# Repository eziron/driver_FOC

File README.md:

# EZFOC V1 - Controlador FOC para Motores Brushless

<p align="center">
  
  <br>
  <em>Vista frontal de la PCB EZFOC V1 completamente ensamblada.</em>
</p>

---

## 📜 Descripción General

**EZFOC V1** es mi proyecto de título con el cual obtuve el grado de Ingeniero de Ejecución en Electrónica. El proyecto se enfoca en el diseño, implementación y validación de un controlador de campo orientado (FOC) para motores brushless (BLDC), desarrollado desde cero abarcando tanto el diseño del **hardware (PCB)** como la programación del **firmware** en un microcontrolador de alto rendimiento **STM32H743VIT6**.

El principal objetivo del proyecto fue ofrecer una solución robusta y de altas prestaciones para aplicaciones exigentes, como la **robótica de competencia (robots de sumo)**, donde el control preciso de torque y velocidad, junto con la capacidad de manejar altas corrientes, es fundamental.

Para una referencia completa y detallada, puedes consultar el **[Esquemático del Hardware](esquematico%20PCB.pdf)** y el **[Manuscrito del Proyecto de Título](manuscrito%20Driver%20FOC%20rev%203%20300325.pdf)**, ambos disponibles en la raíz de este repositorio.

### ✨ Características Principales

*   **Control FOC (Field-Oriented Control):** Permite un control de torque suave y eficiente, desacoplando el flujo magnético del par motor.
*   **Hardware Personalizado:**
    *   PCB de 4 capas diseñada en Autodesk Eagle. Una parte del ensamblaje se realizó mediante el servicio de **PCBA de JLCPCB**, mientras que los componentes restantes fueron soldados manualmente.
    *   Inversor trifásico capaz de manejar altas corrientes (hasta 100A continuos por diseño, con MOSFETs en paralelo).
    *   Medición de corriente de fase **en línea (inline)**, a la salida de cada pierna del inversor, con resistencias shunt y amplificadores INA240.
    *   Soporte para encoder magnético (AS5047P) para una realimentación de posición precisa.
*   **Firmware de Alto Rendimiento:**
    *   Basado en un microcontrolador **STM32H743VIT6** (ARM Cortex-M7 @ 480 MHz).
    *   Lazo de control ejecutado a **48 kHz** en una interrupción de alta prioridad para garantizar el tiempo real.
    *   Uso intensivo de periféricos como Timers, ADC y DMA para minimizar la carga de la CPU.
    *   Comunicación USB (Virtual COM Port) para depuración y visualización de datos en tiempo real.
*   **Diseño Mecánico:** Incluye soportes y acoples para el motor y el encoder diseñados en Autodesk Inventor e impresos en 3D.

---

## 📂 Estructura del Repositorio

El repositorio está organizado en varios directorios clave que separan las diferentes partes del proyecto. Para un acceso rápido, el **esquemático final** (`esquematico PCB.pdf`) y el **manuscrito del proyecto** (`manuscrito Driver FOC...pdf`) se encuentran en la raíz del repositorio.

```
.
├── Firmware_H7/      # Código fuente del firmware para el STM32H7.
├── Hardware/         # Archivos de diseño de la PCB y modelos 3D.
├── datasheets/       # Hojas de datos de los componentes principales.
├── manuscrito/       # Documento de la tesis, gráficos y datos de validación.
├── fotos/            # Fotografías del hardware y montaje.
├── referencias/      # Documentos de referencia y papers utilizados.
└── util/             # Scripts y utilidades para depuración y análisis de datos.
```

### 🧠 `Firmware_H7`

Contiene todo el código fuente para el microcontrolador. El entorno de desarrollo es **VSCode** con la extensión `stm32-for-vscode`.

*   `Board/`: **Lógica de aplicación principal.** Aquí se implementan los módulos clave del controlador:
    *   `FOC.c/.h`: Algoritmo central de FOC (transformadas de Clarke, Park, etc.).
    *   `PID.c/.h`: Controladores PID para los lazos de corriente y velocidad.
    *   `encoder.c/.h`: Lógica para la lectura y procesamiento de datos del encoder.
    *   `state_machine.c/.h`: Máquina de estados para gestionar el funcionamiento del motor (calibración, run, stop).
*   `Core/`: Código base generado por **STM32CubeMX**.
    *   `Src/main.c`: Punto de entrada principal y bucle de baja prioridad.
    *   `Src/stm32h7xx_it.c`: Rutinas de servicio de interrupción (aquí vive el lazo FOC).
*   `Makefile` y `STM32-for-VSCode.config.yaml`: Archivos de configuración para la compilación gestionada por la extensión de VSCode.

### 🛠️ `Hardware`

Todos los archivos de diseño de la placa controladora "EZFOC V1".

*   `3D/`: Archivos de diseño mecánico (`.ipt`, `.iam` de Inventor) y modelos para impresión 3D (`.stl`) del soporte motor-encoder.
*   `EZFOC_V1.sch` y `EZFOC_V1.brd`: Archivos de esquemático y PCB de Autodesk Eagle.
*   `EZFOC_V1_bom.csv` y `EZFOC_V1_cpl.csv`: Lista de materiales (BOM) y archivo de posicionamiento (CPL) para el ensamblaje automatizado.
*   `libs/`: Librerías de componentes para Eagle, obtenidas de diversas fuentes y con algunas modificaciones menores.

### 📊 `manuscrito` y `util`

*   **`manuscrito/`**: Contiene el documento de la tesis en formato LaTeX (`.tex`), junto con todas las imágenes, gráficos y datos (`.csv`) utilizados para la validación del controlador.
*   **`util/`**: Herramientas de apoyo desarrolladas en Python.
    *   `debug_FOC.py`: Script para recibir datos del microcontrolador vía USB, graficarlos en tiempo real y guardarlos en CSV.
    *   `reloj bruto.py`: Script auxiliar para calcular y obtener las configuraciones de los PLLs para el sistema de reloj del STM32H7.
    *   `Debug_LOGS/`: Logs de datos capturados durante las pruebas.

---

## 🚀 Configuración y Uso

Este proyecto está configurado para ser compilado utilizando **Visual Studio Code** con la extensión `stm32-for-vscode`.
(idealmente en linux o wsl)

### Requisitos de Software

1.  **Visual Studio Code**: El editor principal.
2.  **Extensión `stm32-for-vscode`**: Búscala e instálala desde el marketplace de VSCode.
3.  **ARM GCC Toolchain**: El compilador. La extensión `stm32-for-vscode` suele guiar en su instalación.
4.  **STM32CubeProgrammer**: Herramienta para flashear el firmware en el microcontrolador.

---

## 📈 Futuras Mejoras y Problemas Conocidos

Este proyecto sienta una base sólida, pero existen varias áreas de mejora identificadas durante el desarrollo:

*   **Protección de Hardware**: Implementar un gate driver con protección anti-*shoot-through* integrada para mejorar la robustez del puente H.
*   **Optimización de Firmware**: Migrar el código a C++ y utilizar un sistema operativo de tiempo real como **FreeRTOS** para una mejor organización y escalabilidad.
*   **Filtrado de Señal**: Mejorar el filtrado de la corriente, ya sea con filtros analógicos pasivos en la PCB o algoritmos de filtrado digital más avanzados.
*   **Compensación de *Cogging Torque***: Implementar un algoritmo de calibración para reducir las vibraciones del motor a bajas velocidades.

## ✒️ Autor

*   **Rodrigo Fuentes Pedreros** - [eziron](https://github.com/eziron)

Un proyecto desarrollado para la **Universidad del Bío-Bío, Facultad de Ingeniería**.

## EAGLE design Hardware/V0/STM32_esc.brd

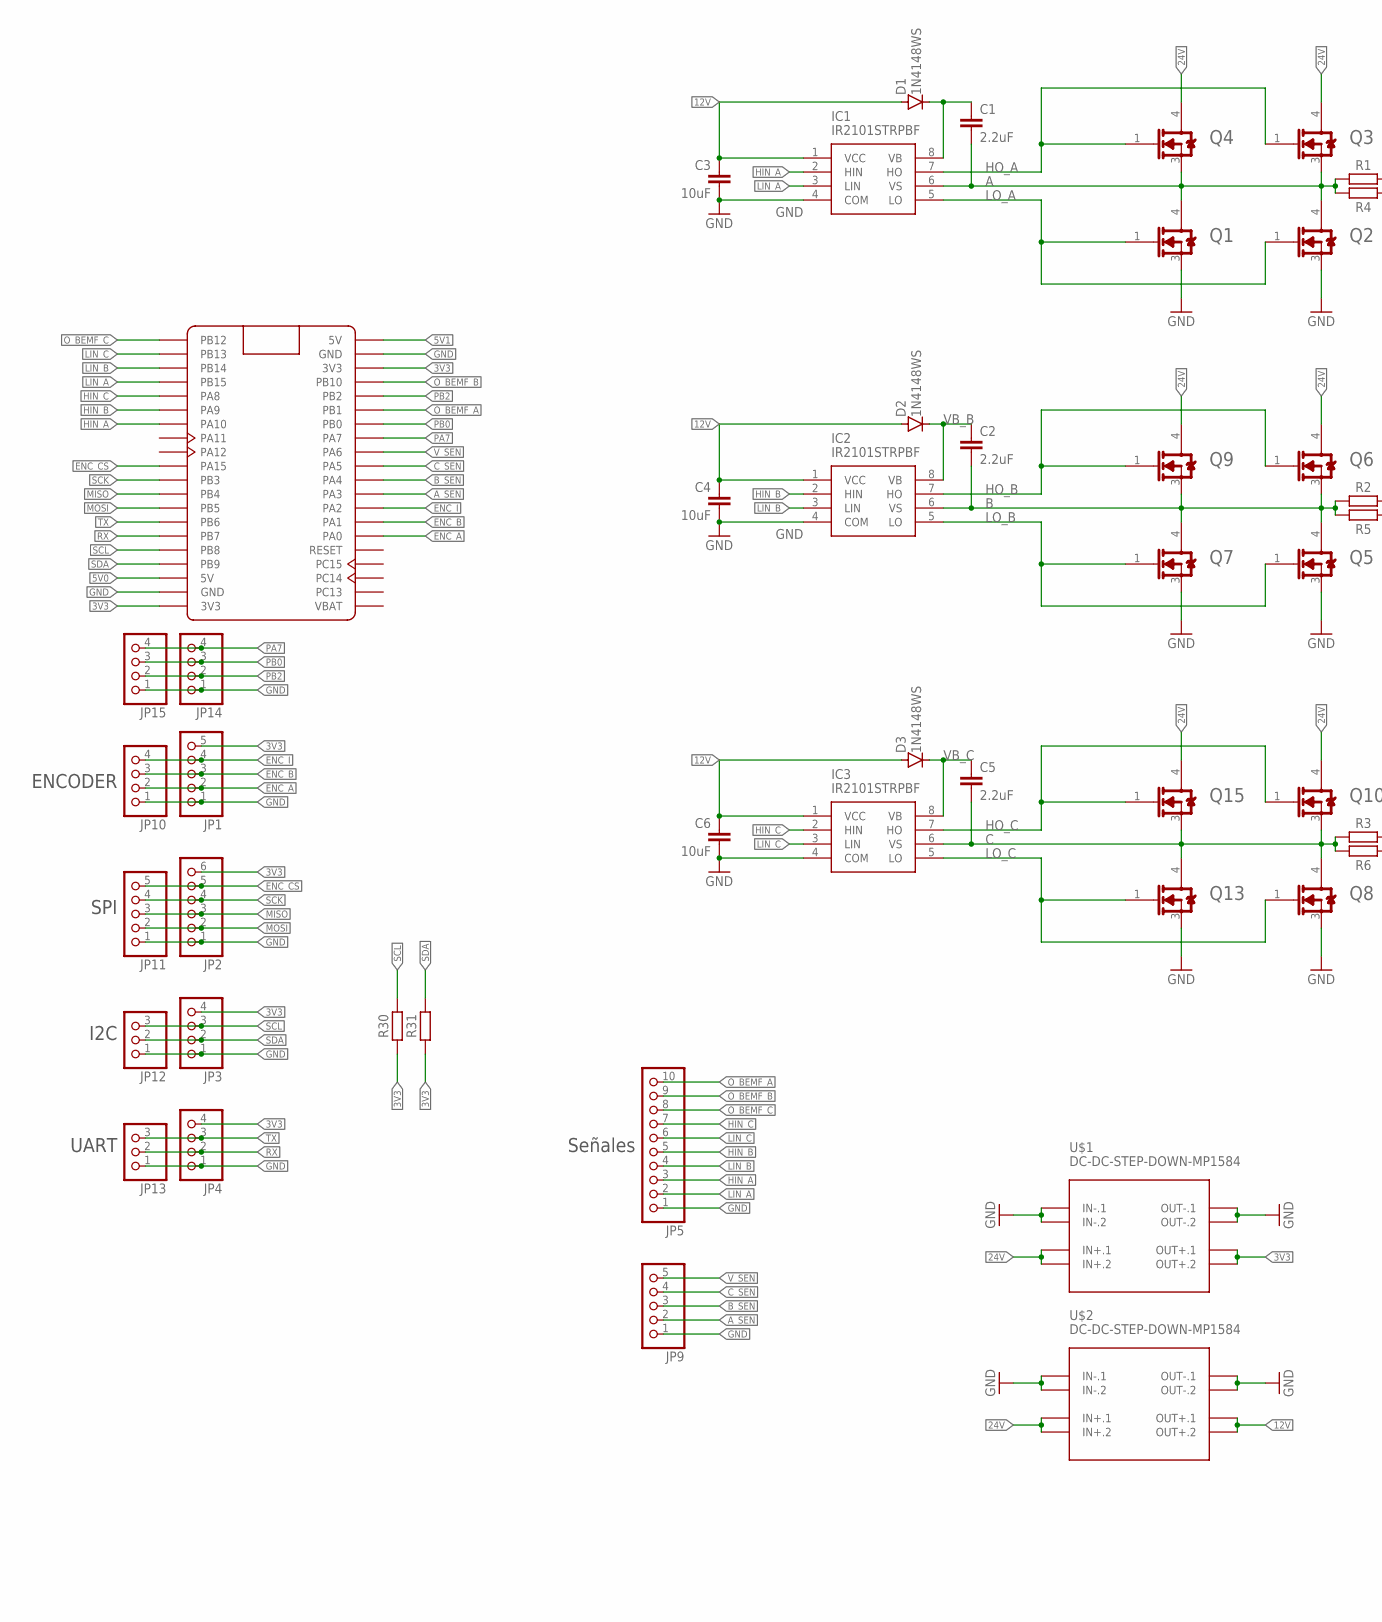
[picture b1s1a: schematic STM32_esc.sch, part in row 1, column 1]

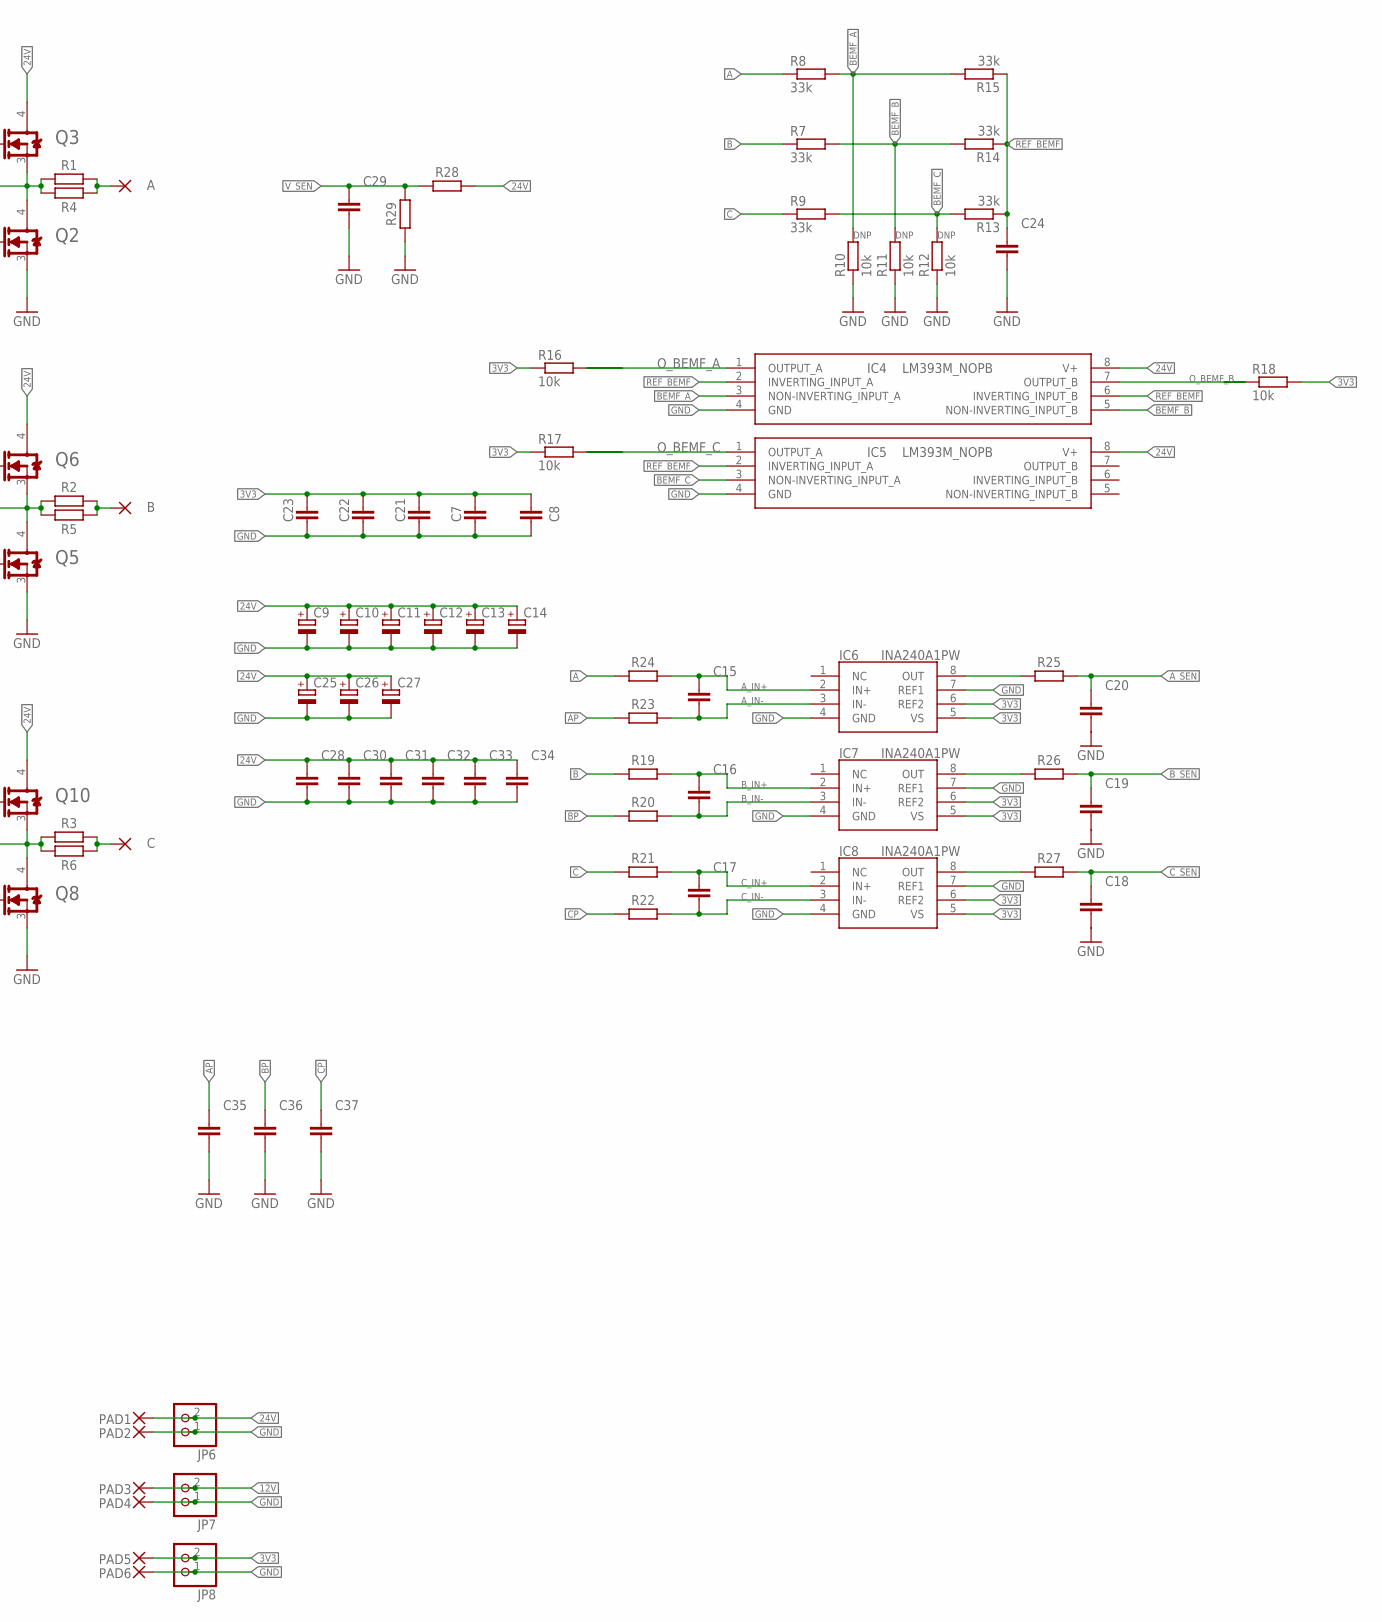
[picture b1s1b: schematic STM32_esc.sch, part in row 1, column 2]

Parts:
A: SMD5; SMD2,54-5,08
B: SMD5; SMD2,54-5,08
C: SMD5; SMD2,54-5,08
C1, C2, C5: 2.2uF; CAPC3216X135
C3, C4, C6: 10uF; CAPC3216X135
C7, C8, C15, C16, C17, C18, C19, C20, C21, C22, C23, C24, C29: C_CHIP-0603(1608-METRIC); 0603
C9, C10, C11, C12, C13, C14: C-POL_TANTALUM-2917(7343-METRIC); CAPMP7343X310N
C25, C26, C27: C-POL_ECAP-10.5MM; CAPAE1030X1050N
C28, C30, C31, C32, C33, C34, C35, C36, C37: C_CHIP-1206(3216-METRIC); 1206
D1, D2, D3: 1N4148WS; DO35-10
IC1, IC2, IC3: IR2101STRPBF; SOIC127P600X175-8N
IC4, IC5: LM393M_NOPB; SOIC127P600X175-8N
IC6, IC7, IC8: INA240A1PW; SOP65P640X120-8N
JP1, JP9, JP11: PINHD-1X5; 1X05
JP2: PINHD-1X6; 1X06
JP3, JP4, JP10, JP14, JP15: PINHD-1X4; 1X04
JP5: PINHD-1X10; 1X10
JP6, JP7, JP8: PINHD-1X2; 1X02
JP12, JP13: PINHD-1X3; 1X03
PAD1, PAD2, PAD3, PAD4, PAD5, PAD6: PAD1.27X2.54; SMD1,27-2,54
Q1, Q2, Q3, Q4, Q5, Q6, Q7, Q8, Q9, Q10, Q13, Q15: INFINEON_IRLR7843TRPBFINFINEON_IRLR7843TRPBF_0_0; INFINEON_IRLR7843TRPBF_0
R1, R2, R3, R4, R5, R6: R_CHIP-2512(6332-METRIC); 2512
R7, R8, R9, R13, R14, R15: 33k; 0603
R10, R11, R12, R16, R17, R18: 10k; 0603
R19, R20, R21, R22, R23, R24, R25, R26, R27, R28, R29, R30, R31: R_CHIP-0603(1608-METRIC); 0603
U1: STM32F4X1; BLACK_PILL
U$1, U$2: DC-DC-STEP-DOWN-MP1584

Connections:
3V3: C7.1, C8.1, C21.1, C22.1, C23.1, IC6.5 (VS), IC6.6 (REF2), IC7.5 (VS), IC7.6 (REF2), IC8.5 (VS), IC8.6 (REF2), JP1.5, JP2.6, JP3.4, JP4.4, JP8.2, PAD5.1, R16.1, R17.1, R18.2, R30.1, R31.1, U1.P$20 (3.3V1), U1.P$23 (3V3), U$1.OUT+.1, U$1.OUT+.2
5V0: U1.P$18 (5V)
5V1: U1.P$21 (5V0)
12V: C3.2, C4.2, C6.2, D1.A, D2.A, D3.A, IC1.1 (VCC), IC2.1 (VCC), IC3.1 (VCC), JP7.2, PAD3.1, U$2.OUT+.1, U$2.OUT+.2
24V: C9.1 (+), C10.1 (+), C11.1 (+), C12.1 (+), C13.1 (+), C14.1 (+), C25.1 (+), C26.1 (+), C27.1 (+), C28.1, C30.1, C31.1, C32.1, C33.1, C34.1, IC4.8 (V+), IC5.8 (V+), JP6.2, PAD1.1, Q3.4 (DRAIN), Q4.4 (DRAIN), Q6.4 (DRAIN), Q9.4 (DRAIN), Q10.4 (DRAIN), Q15.4 (DRAIN), R28.2, U$1.IN+.1, U$1.IN+.2, U$2.IN+.1, U$2.IN+.2
A: C1.2, IC1.6 (VS), Q1.4 (DRAIN), Q2.4 (DRAIN), Q3.3 (SOURCE), Q4.3 (SOURCE), R1.1, R4.2, R8.1, R24.1
AP: A.1, C35.1, R1.2, R4.1, R23.1
A_IN+: C15.1, IC6.2 (IN+), R24.2
A_IN-: C15.2, IC6.3 (IN-), R23.2
A_OUT_SEN: IC6.8 (OUT), R25.1
A_SEN: C20.1, JP9.2, R25.2, U1.P$32 (PA3)
B: C2.2, IC2.6 (VS), Q5.4 (DRAIN), Q6.3 (SOURCE), Q7.4 (DRAIN), Q9.3 (SOURCE), R2.1, R5.2, R7.1, R19.1
BEMF_A: IC4.3 (NON-INVERTING_INPUT_A), R8.2, R10.2, R15.2
BEMF_B: IC4.5 (NON-INVERTING_INPUT_B), R7.2, R11.2, R14.2
BEMF_C: IC5.3 (NON-INVERTING_INPUT_A), R9.2, R12.2, R13.2
BP: B.1, C36.1, R2.2, R5.1, R20.1
B_IN+: C16.1, IC7.2 (IN+), R19.2
B_IN-: C16.2, IC7.3 (IN-), R20.2
B_OUT_SEN: IC7.8 (OUT), R26.1
B_SEN: C19.1, JP9.3, R26.2, U1.P$31 (PA4)
C: C5.2, IC3.6 (VS), Q8.4 (DRAIN), Q10.3 (SOURCE), Q13.4 (DRAIN), Q15.3 (SOURCE), R3.1, R6.2, R9.1, R21.1
CP: C.1, C37.1, R3.2, R6.1, R22.1
C_IN+: C17.1, IC8.2 (IN+), R21.2
C_IN-: C17.2, IC8.3 (IN-), R22.2
C_OUT_SEN: IC8.8 (OUT), R27.1
C_SEN: C18.1, JP9.4, R27.2, U1.P$30 (PA5)
ENC_A: JP1.2, JP10.2, U1.P$35 (PA0)
ENC_B: JP1.3, JP10.3, U1.P$34 (PA1)
ENC_CS: JP2.5, JP11.5, U1.P$10 (PA15)
ENC_I: JP1.4, JP10.4, U1.P$33 (PA2)
GND: C3.1, C4.1, C6.1, C7.2, C8.2, C9.2 (-), C10.2 (-), C11.2 (-), C12.2 (-), C13.2 (-), C14.2 (-), C18.2, C19.2, C20.2, C21.2, C22.2, C23.2, C24.2, C25.2 (-), C26.2 (-), C27.2 (-), C28.2, C29.2, C30.2, C31.2, C32.2, C33.2, C34.2, C35.2, C36.2, C37.2, IC1.4 (COM), IC2.4 (COM), IC3.4 (COM), IC4.4 (GND), IC5.4 (GND), IC6.4 (GND), IC6.7 (REF1), IC7.4 (GND), IC7.7 (REF1), IC8.4 (GND), IC8.7 (REF1), JP1.1, JP2.1, JP3.1, JP4.1, JP5.1, JP6.1, JP7.1, JP8.1, JP9.1, JP10.1, JP11.1, JP12.1, JP13.1, JP14.1, JP15.1, PAD2.1, PAD4.1, PAD6.1, Q1.3 (SOURCE), Q2.3 (SOURCE), Q5.3 (SOURCE), Q7.3 (SOURCE), Q8.3 (SOURCE), Q13.3 (SOURCE), R10.1, R11.1, R12.1, R29.1, U1.P$19 (GND2), U1.P$22 (GND), U$1.IN-.1, U$1.IN-.2, U$1.OUT-.1, U$1.OUT-.2, U$2.IN-.1, U$2.IN-.2, U$2.OUT-.1, U$2.OUT-.2
HIN_A: IC1.2 (HIN), JP5.3, U1.P$7 (PA10)
HIN_B: IC2.2 (HIN), JP5.5, U1.P$6 (PA9)
HIN_C: IC3.2 (HIN), JP5.7, U1.P$5 (PA8)
HO_A: IC1.7 (HO), Q3.1 (GATE), Q4.1 (GATE)
HO_B: IC2.7 (HO), Q6.1 (GATE), Q9.1 (GATE)
HO_C: IC3.7 (HO), Q10.1 (GATE), Q15.1 (GATE)
LIN_A: IC1.3 (LIN), JP5.2, U1.P$4 (PB15)
LIN_B: IC2.3 (LIN), JP5.4, U1.P$3 (PB14)
LIN_C: IC3.3 (LIN), JP5.6, U1.P$2 (PB13)
LO_A: IC1.5 (LO), Q1.1 (GATE), Q2.1 (GATE)
LO_B: IC2.5 (LO), Q5.1 (GATE), Q7.1 (GATE)
LO_C: IC3.5 (LO), Q8.1 (GATE), Q13.1 (GATE)
MISO: JP2.3, JP11.3, U1.P$12 (PB4)
MOSI: JP2.2, JP11.2, U1.P$13 (PB5)
O_BEMF_A: IC4.1 (OUTPUT_A), JP5.10, R16.2, U1.P$26 (PB1)
O_BEMF_B: IC4.7 (OUTPUT_B), JP5.9, R18.1, U1.P$24 (PB10)
O_BEMF_C: IC5.1 (OUTPUT_A), JP5.8, R17.2, U1.P$1 (PB12)
PA7: JP14.4, JP15.4, U1.P$28 (PA7)
PB0: JP14.3, JP15.3, U1.P$27 (PB0)
PB2: JP14.2, JP15.2, U1.P$25 (PB2)
REF_BEMF: C24.1, IC4.2 (INVERTING_INPUT_A), IC4.6 (INVERTING_INPUT_B), IC5.2 (INVERTING_INPUT_A), R13.1, R14.1, R15.1
RX: JP4.2, JP13.2, U1.P$15 (PB7)
SCK: JP2.4, JP11.4, U1.P$11 (PB3)
SCL: JP3.3, JP12.3, R30.2, U1.P$16 (PB8)
SDA: JP3.2, JP12.2, R31.2, U1.P$17 (PB9)
TX: JP4.3, JP13.3, U1.P$14 (PB6)
VBAT: U1.P$40 (VBAT)
VB_A: C1.1, D1.C, IC1.8 (VB)
VB_B: C2.1, D2.C, IC2.8 (VB)
VB_C: C5.1, D3.C, IC3.8 (VB)
V_SEN: C29.1, JP9.5, R28.1, R29.2, U1.P$29 (PA6)

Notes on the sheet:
ENCODER
SPI
I2C
UART
Señales

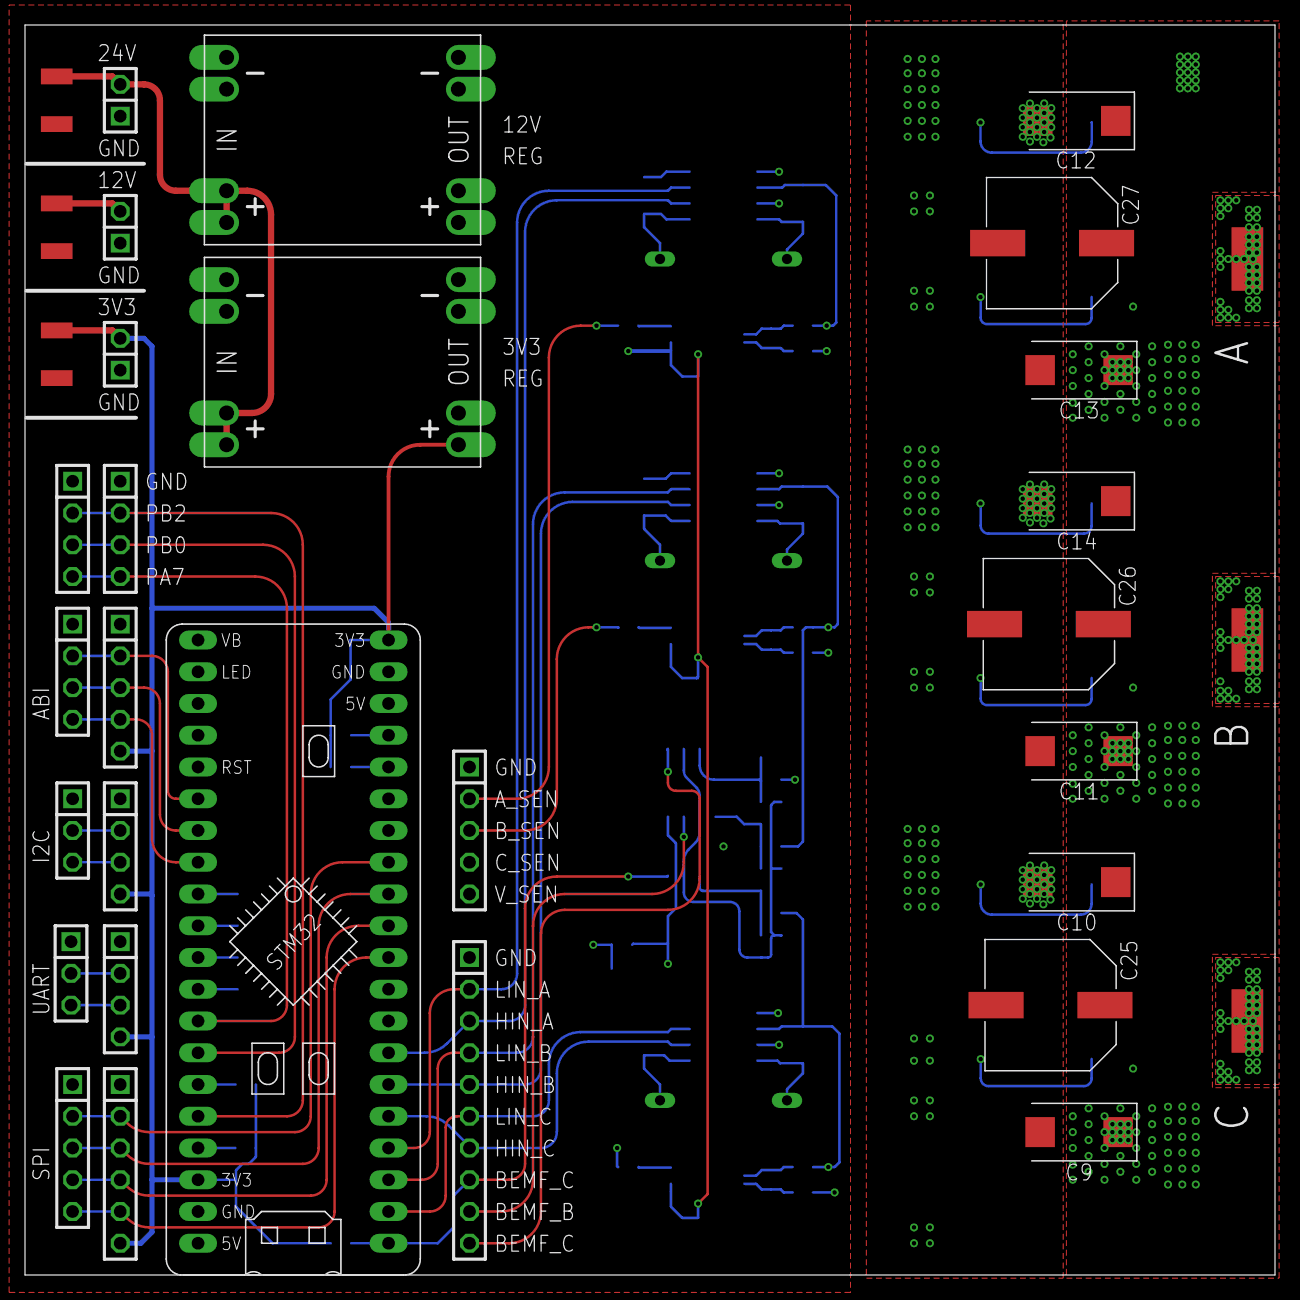
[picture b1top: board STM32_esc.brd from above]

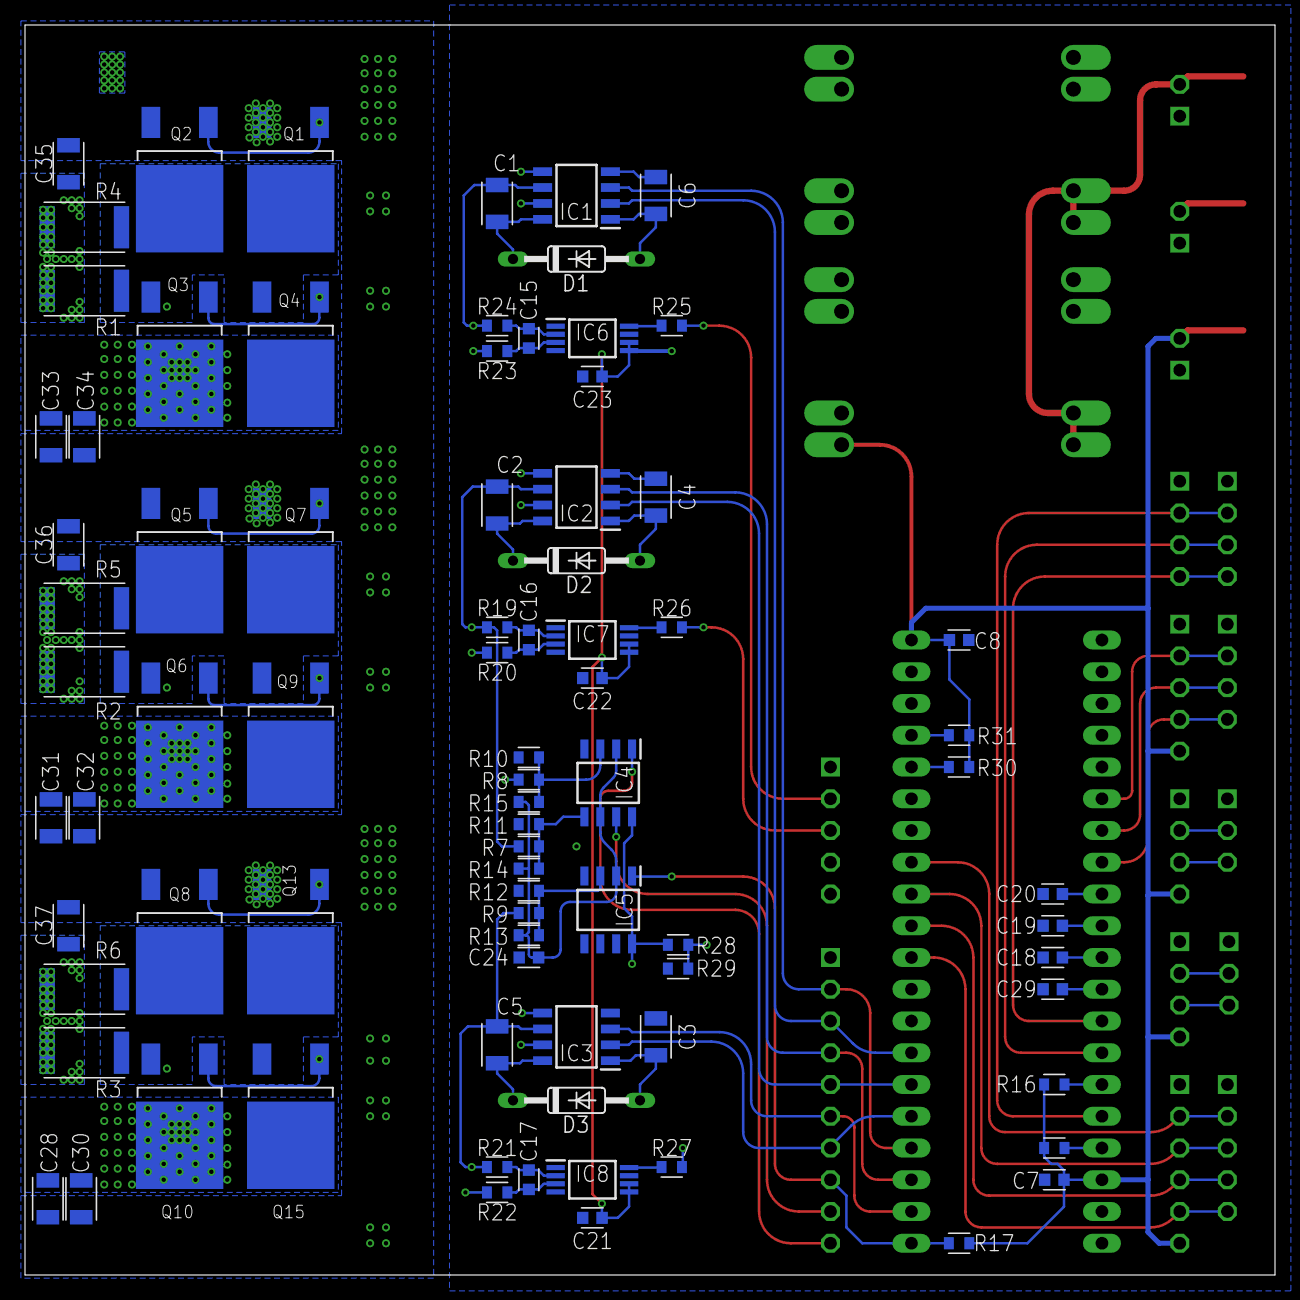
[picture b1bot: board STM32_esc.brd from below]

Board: 4 copper layers, 100.0 x 100.0 mm, 118 parts (82 on the bottom side), 59 nets.

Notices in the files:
parts and their libraries:
diy-modules: Released under the Creative Commons Attribution 4.0 International License: http://creativecommons.org/licenses/by/4.0
